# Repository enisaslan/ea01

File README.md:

# ea01
Plant Irrigation Controller

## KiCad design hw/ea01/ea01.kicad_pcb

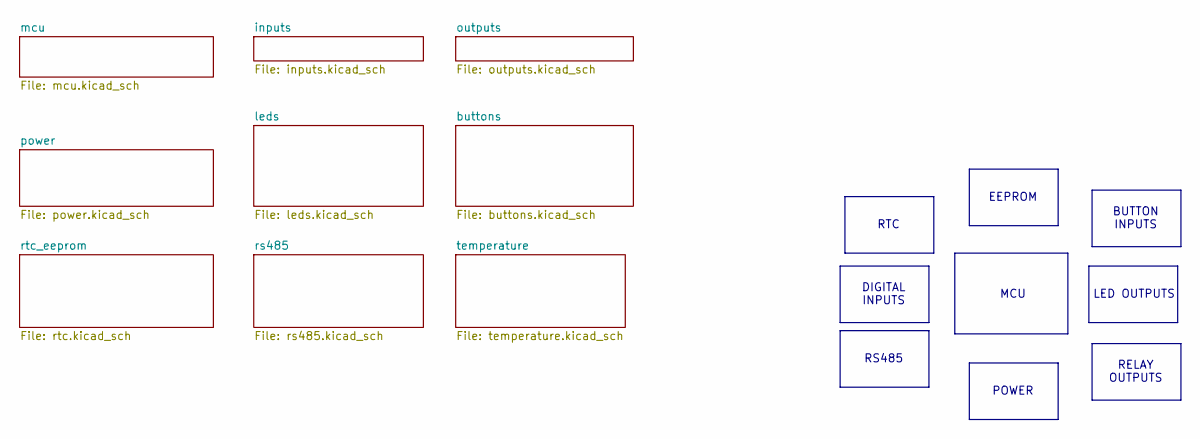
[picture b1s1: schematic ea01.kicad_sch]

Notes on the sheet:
DIGITAL INPUTS
EEPROM
LED OUTPUTS
MCU
RS485
RTC
BUTTON INPUTS
POWER
RELAY OUTPUTS

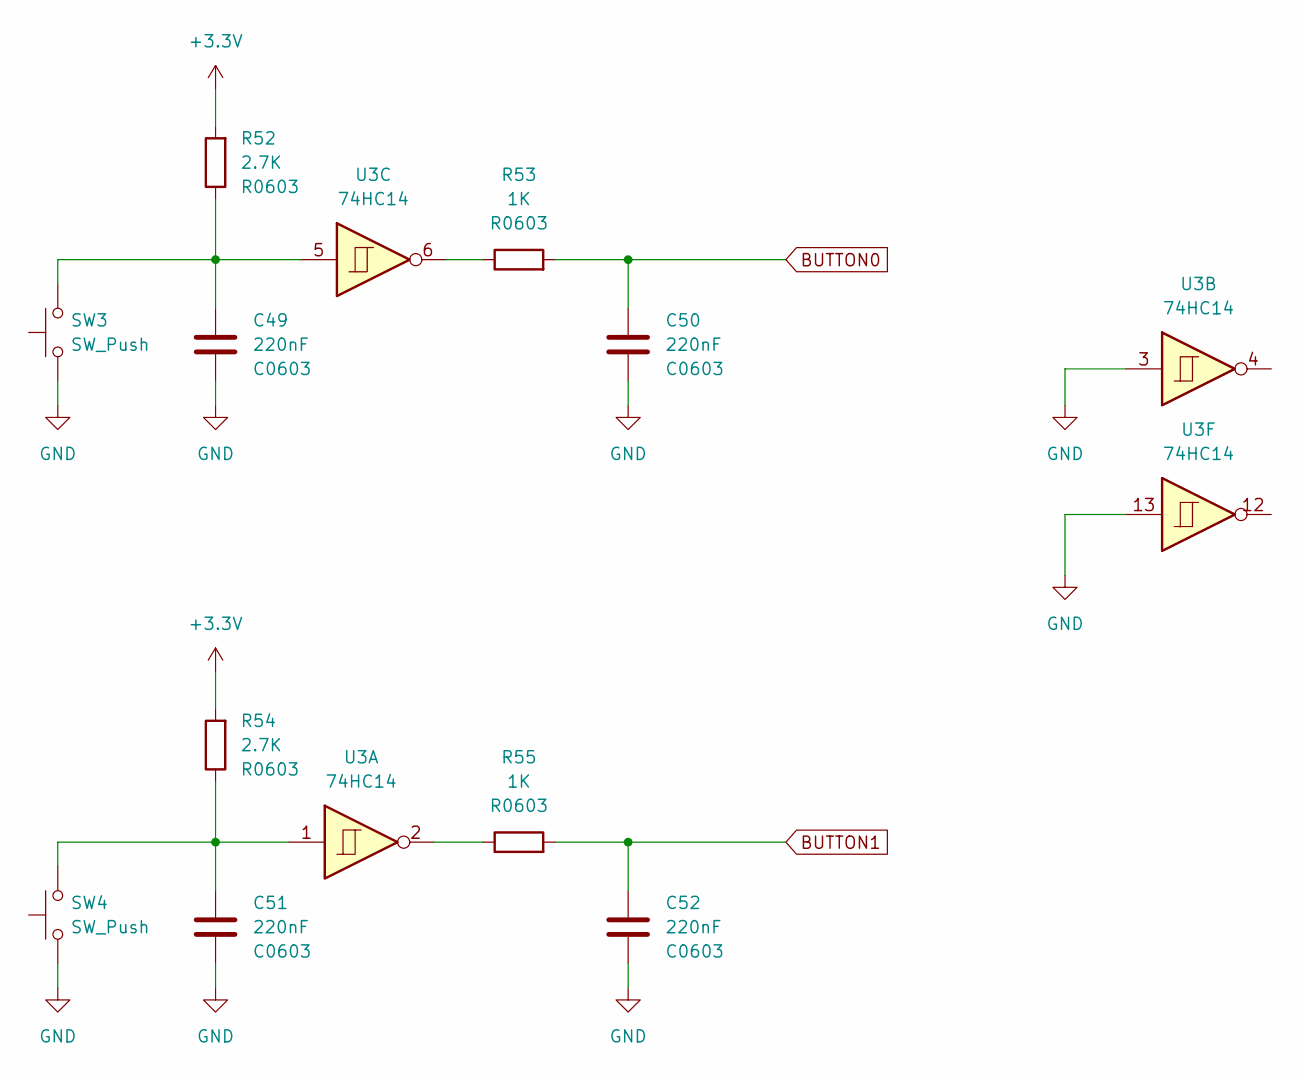
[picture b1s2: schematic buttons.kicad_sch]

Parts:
C49, C50, C51, C52: 220nF; C_0603_1608Metric
R52, R54: 2.7K; R_0603_1608Metric
R53, R55: 1K; R_0603_1608Metric
SW3, SW4: SW_Push; SW_PUSH_6mm_H5mm
U3: 74HC14; SOIC-14_3.9x8.7mm_P1.27mm

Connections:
+3.3V: R52.2, R54.2; also elsewhere on the board
BUTTON0: C50.1, R53.2; also elsewhere on the board
BUTTON1: C52.1, R55.2; also elsewhere on the board
GND: C49.2, C50.2, C51.2, C52.2, SW3.1, SW4.1, U3.3, U3.13; also elsewhere on the board
unnamed: C49.1, R52.1, SW3.2, U3.5
unnamed: C51.1, R54.1, SW4.2, U3.1
unnamed: R53.1, U3.6
unnamed: R55.1, U3.2

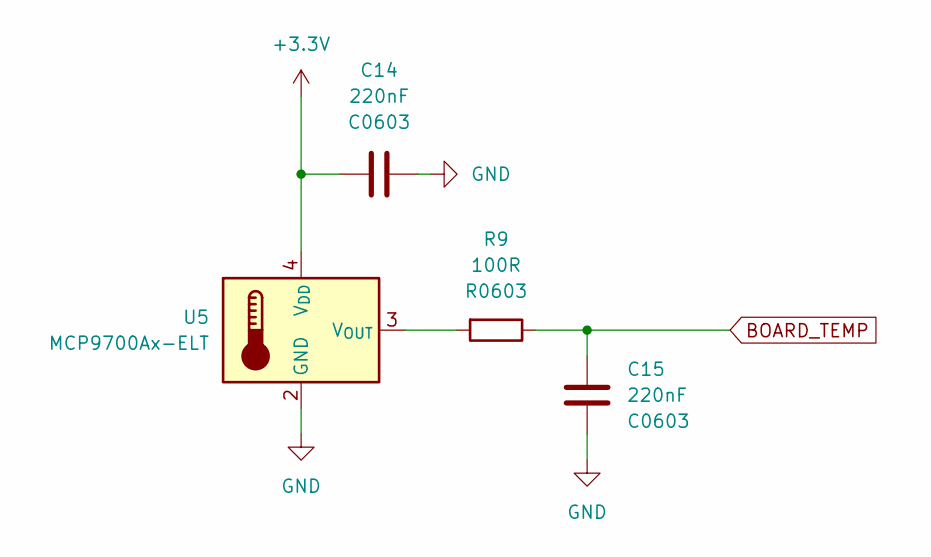
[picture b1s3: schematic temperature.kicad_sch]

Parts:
C14, C15: 220nF; C_0603_1608Metric
R9: 100R; R_0603_1608Metric
U5: MCP9700Ax-ELT; SOT-353_SC-70-5

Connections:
+3.3V: C14.1, U5.4 (V_{DD}); also elsewhere on the board
BOARD_TEMP: C15.1, R9.1; also elsewhere on the board
GND: C14.2, C15.2, U5.2 (GND); also elsewhere on the board
unnamed: R9.2, U5.3 (V_{OUT})

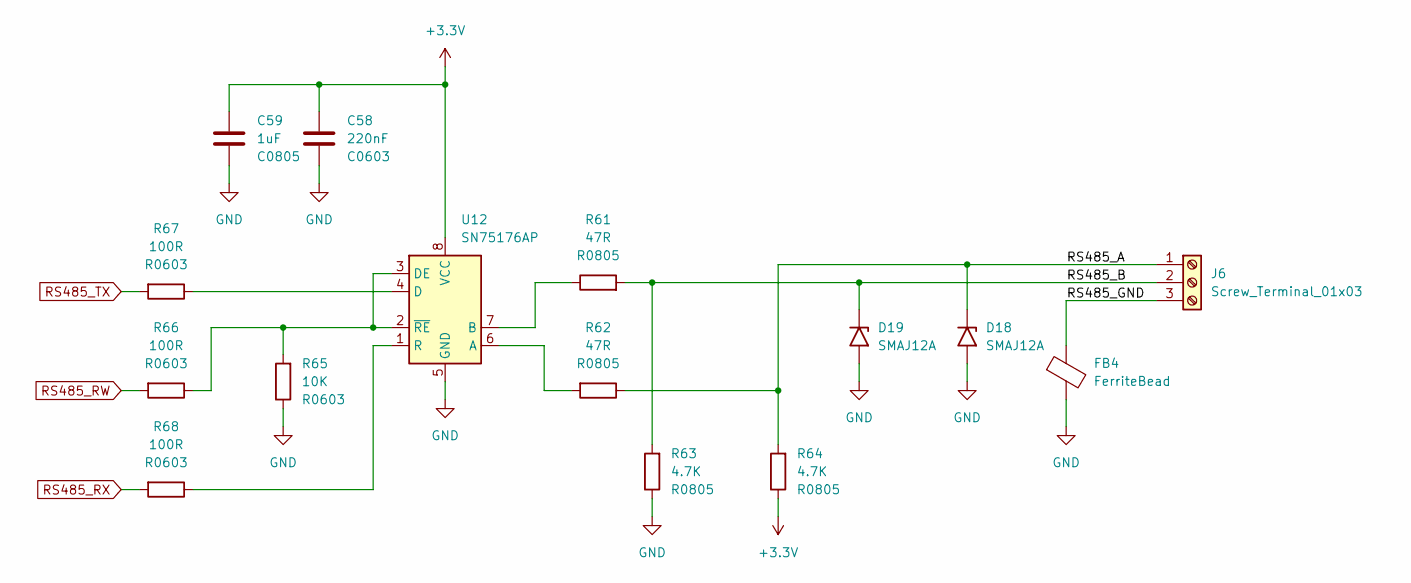
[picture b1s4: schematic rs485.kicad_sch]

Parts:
C58: 220nF; C_0603_1608Metric
C59: 1uF; C_0805_2012Metric
D18, D19: SMAJ12A; D_SMA
FB4: FerriteBead; R_0805_2012Metric
J6: Screw_Terminal_01x03; TerminalBlock_bornier-3_P5.08mm
R61, R62: 47R; R_0805_2012Metric
R63, R64: 4.7K; R_0805_2012Metric
R65: 10K; R_0603_1608Metric
R66, R67, R68: 100R; R_0603_1608Metric
U12: SN75176AP; DIP-8_W7.62mm

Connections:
+3.3V: C58.1, C59.1, R64.1, U12.8 (VCC); also elsewhere on the board
/rs485/RS485_A: D18.1 (A1), J6.1, R62.1, R64.2
/rs485/RS485_B: D19.1 (A1), J6.2, R61.2, R63.2
/rs485/RS485_GND: FB4.1, J6.3
GND: C58.2, C59.2, D18.2 (A2), D19.2 (A2), FB4.2, R63.1, R65.1, U12.5 (GND); also elsewhere on the board
unnamed: R62.2, U12.6 (A)
unnamed: R61.1, U12.7 (B)
unnamed: R67.1, U12.4 (D)
unnamed: R65.2, R66.1, U12.2 (~RE), U12.3 (DE)
unnamed: R68.1, U12.1 (R)
RS485_RW: R66.2; also elsewhere on the board
RS485_RX: R68.2; also elsewhere on the board
RS485_TX: R67.2; also elsewhere on the board

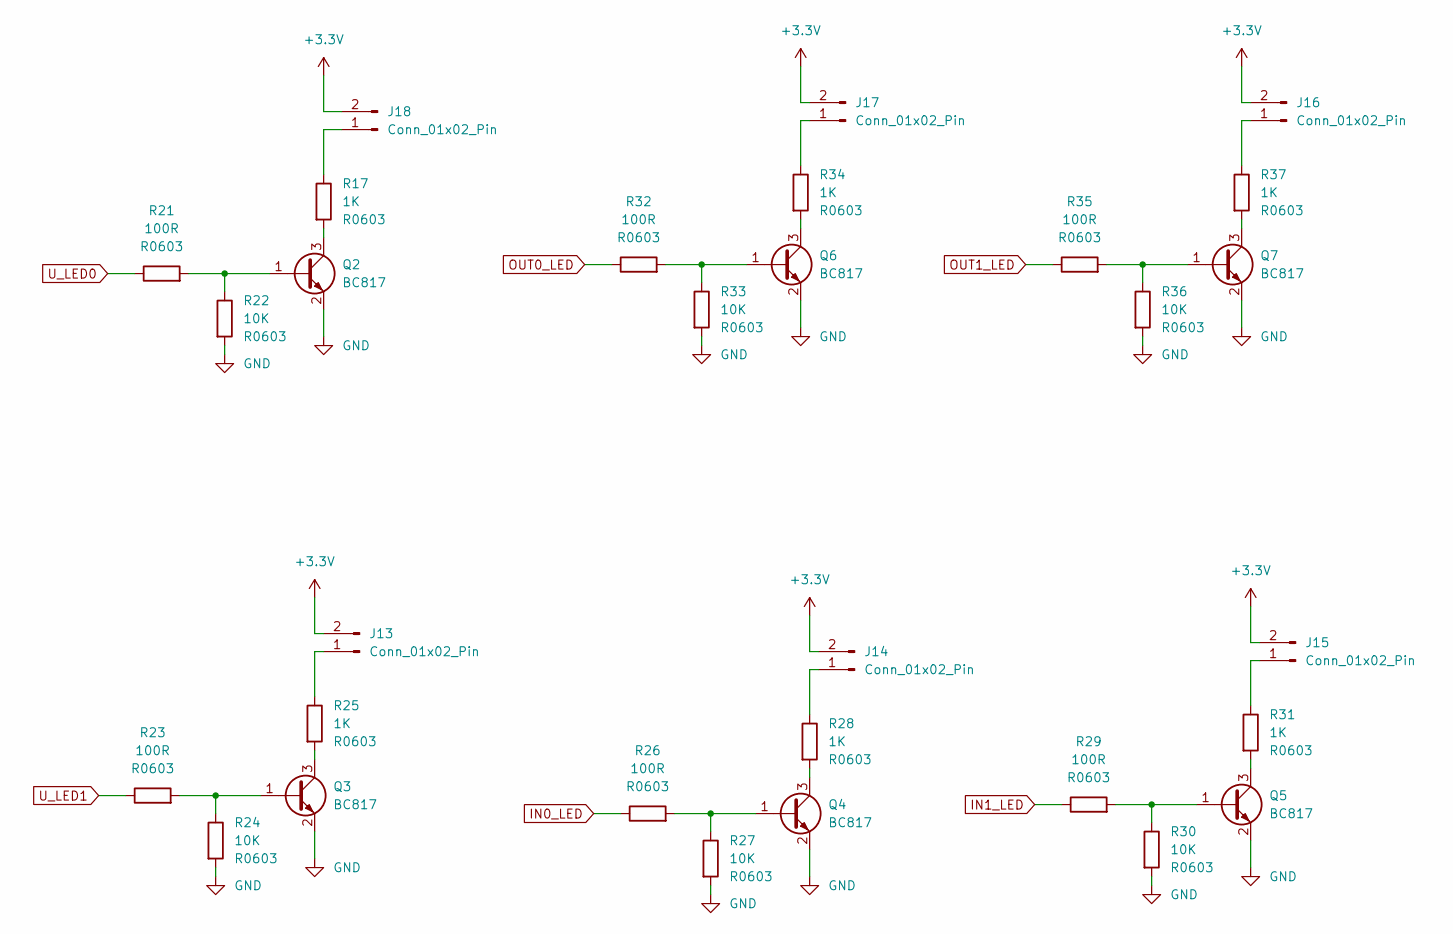
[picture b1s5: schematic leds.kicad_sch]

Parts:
J13, J14, J15, J16, J17, J18: Conn_01x02_Pin; PinHeader_1x02_P1.27mm_Vertical
Q2, Q3, Q4, Q5, Q6, Q7: BC817; SOT-23
R17, R25, R28, R31, R34, R37: 1K; R_0603_1608Metric
R21, R23, R26, R29, R32, R35: 100R; R_0603_1608Metric
R22, R24, R27, R30, R33, R36: 10K; R_0603_1608Metric

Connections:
+3.3V: J13.2, J14.2, J15.2, J16.2, J17.2, J18.2; also elsewhere on the board
GND: Q2.2 (E), Q3.2 (E), Q4.2 (E), Q5.2 (E), Q6.2 (E), Q7.2 (E), R22.2, R24.2, R27.2, R30.2, R33.2, R36.2; also elsewhere on the board
IN0_LED: R26.1; also elsewhere on the board
IN1_LED: R29.1; also elsewhere on the board
unnamed: J13.1, R25.1
unnamed: J14.1, R28.1
unnamed: J15.1, R31.1
unnamed: J16.1, R37.1
unnamed: J17.1, R34.1
unnamed: J18.1, R17.1
unnamed: Q2.1 (B), R21.2, R22.1
unnamed: Q2.3 (C), R17.2
unnamed: Q3.1 (B), R23.2, R24.1
unnamed: Q3.3 (C), R25.2
unnamed: Q4.1 (B), R26.2, R27.1
unnamed: Q4.3 (C), R28.2
unnamed: Q5.1 (B), R29.2, R30.1
unnamed: Q5.3 (C), R31.2
unnamed: Q6.1 (B), R32.2, R33.1
unnamed: Q6.3 (C), R34.2
unnamed: Q7.1 (B), R35.2, R36.1
unnamed: Q7.3 (C), R37.2
OUT0_LED: R32.1; also elsewhere on the board
OUT1_LED: R35.1; also elsewhere on the board
U_LED0: R21.1; also elsewhere on the board
U_LED1: R23.1; also elsewhere on the board

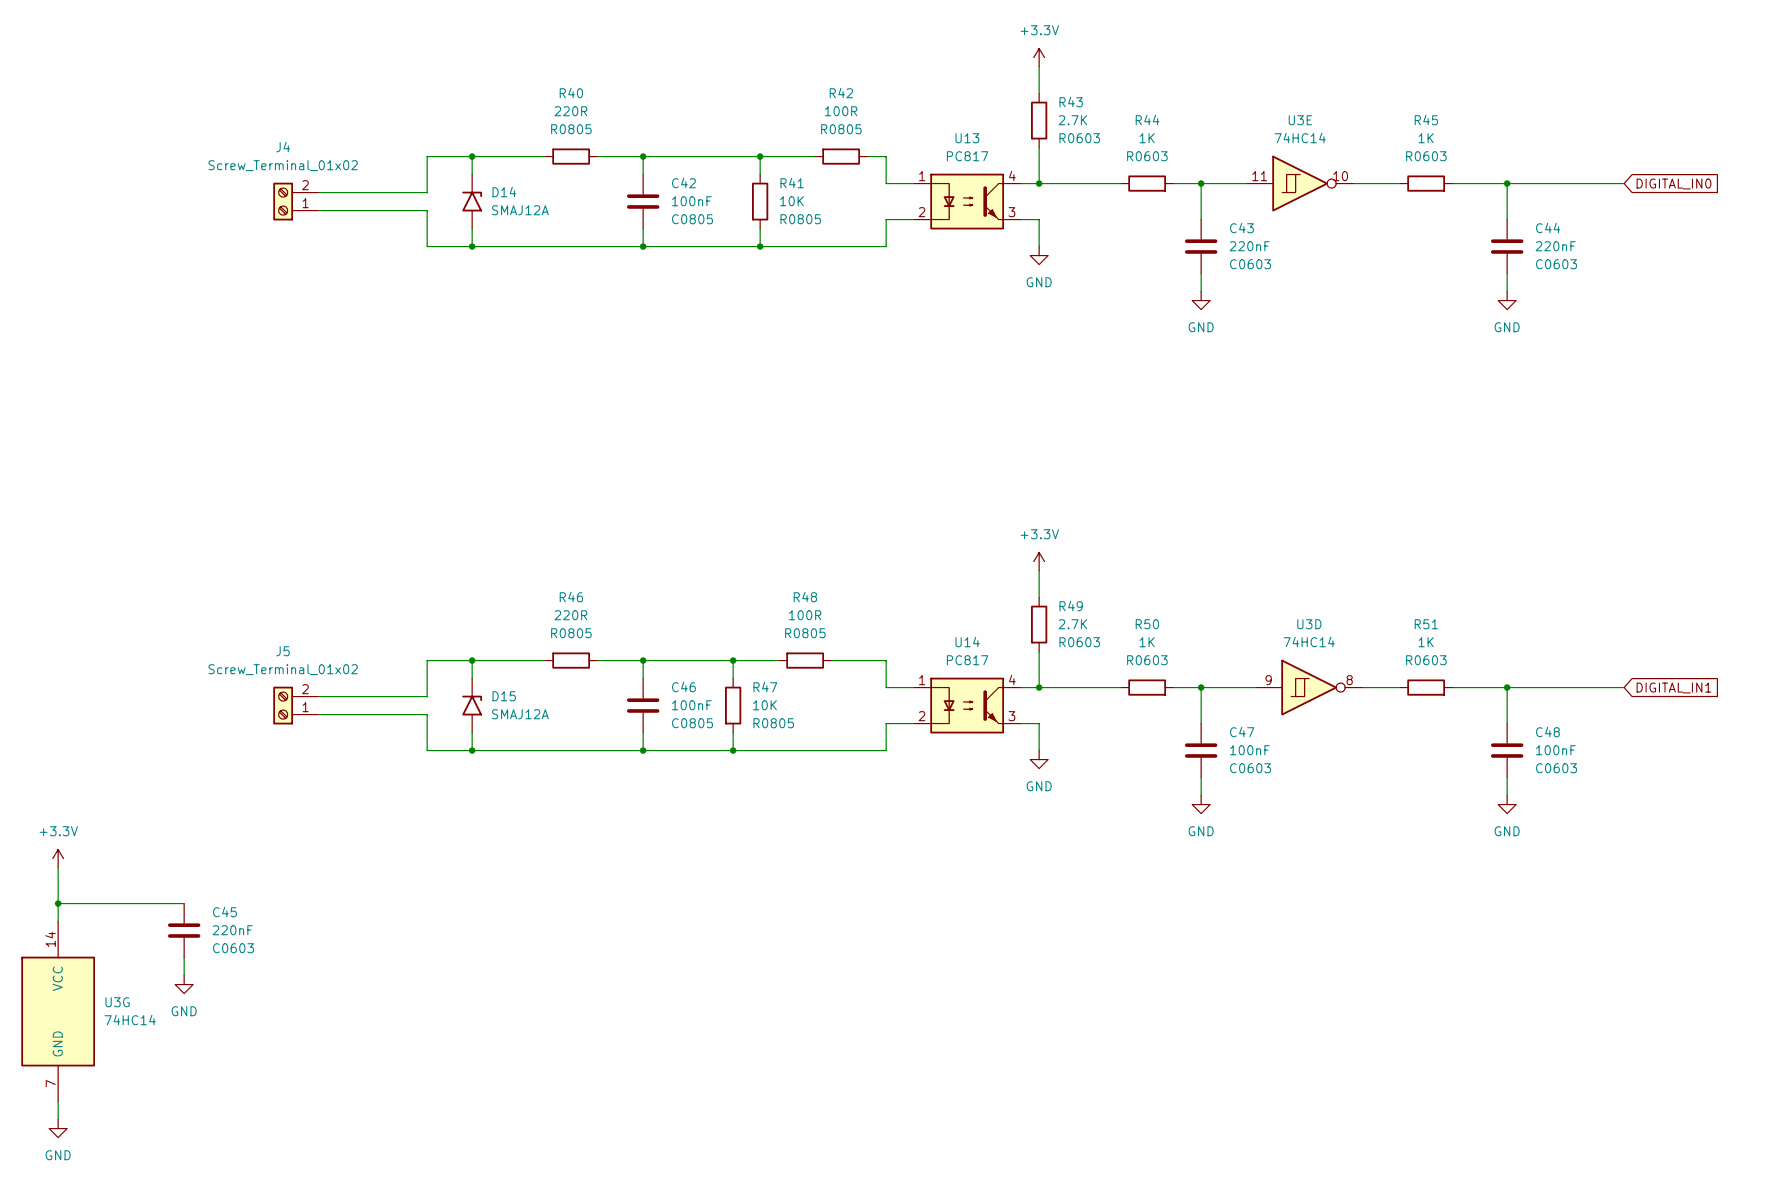
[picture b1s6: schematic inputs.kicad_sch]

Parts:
C42, C46: 100nF; C_0805_2012Metric
C43, C44, C45: 220nF; C_0603_1608Metric
C47, C48: 100nF; C_0603_1608Metric
D14, D15: SMAJ12A; D_SMA
J4, J5: Screw_Terminal_01x02; TerminalBlock_bornier-2_P5.08mm
R40, R46: 220R; R_0805_2012Metric
R41, R47: 10K; R_0805_2012Metric
R42, R48: 100R; R_0805_2012Metric
R43, R49: 2.7K; R_0603_1608Metric
R44, R45, R50, R51: 1K; R_0603_1608Metric
U3: 74HC14; SOIC-14_3.9x8.7mm_P1.27mm
U13, U14: PC817; DIP-4_W7.62mm

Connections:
+3.3V: C45.1, R43.1, R49.1, U3.14 (VCC); also elsewhere on the board
DIGITAL_IN0: C44.1, R45.2; also elsewhere on the board
DIGITAL_IN1: C48.1, R51.2; also elsewhere on the board
GND: C43.2, C44.2, C45.2, C47.2, C48.2, U3.7 (GND), U13.3, U14.3; also elsewhere on the board
unnamed: C42.1, R40.1, R41.1, R42.2
unnamed: C43.1, R44.2, U3.11
unnamed: C46.1, R46.1, R47.1, R48.2
unnamed: C47.1, R50.2, U3.9
unnamed: D14.1 (A1), J4.2, R40.2
unnamed: C42.2, D14.2 (A2), J4.1, R41.2, U13.2
unnamed: D15.1 (A1), J5.2, R46.2
unnamed: C46.2, D15.2 (A2), J5.1, R47.2, U14.2
unnamed: R42.1, U13.1
unnamed: R43.2, R44.1, U13.4
unnamed: R45.1, U3.10
unnamed: R48.1, U14.1
unnamed: R49.2, R50.1, U14.4
unnamed: R51.1, U3.8

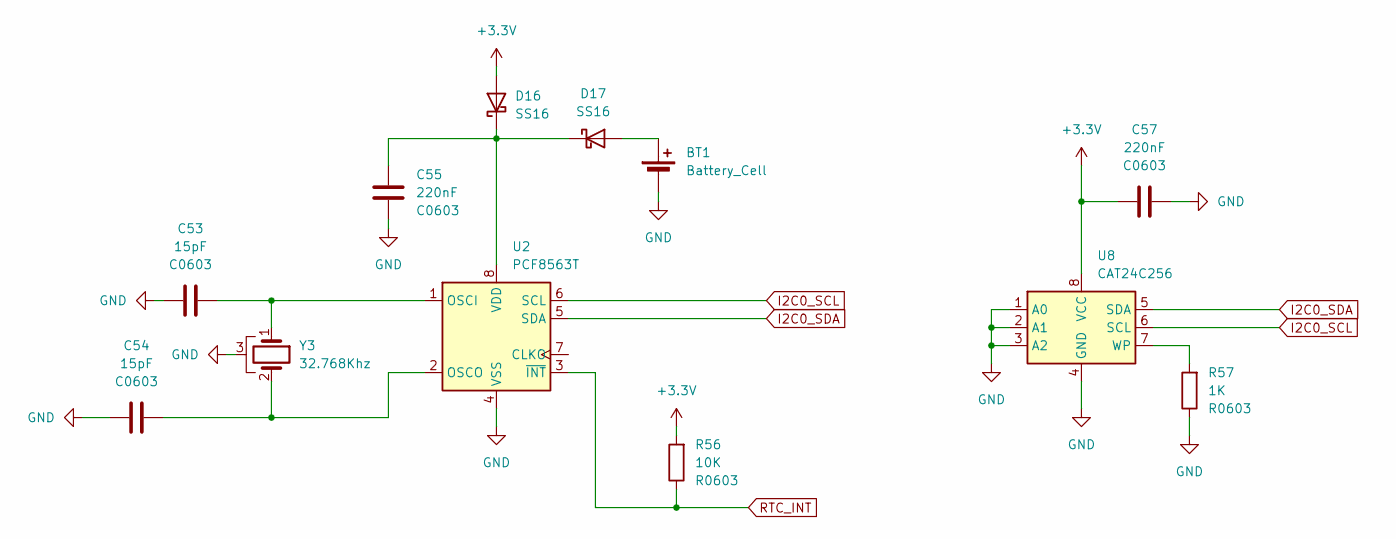
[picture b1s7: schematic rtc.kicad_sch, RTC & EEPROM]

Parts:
BT1: Battery_Cell; PinHeader_1x02_P2.54mm_Vertical
C53, C54: 15pF; C_0603_1608Metric
C55, C57: 220nF; C_0603_1608Metric
D16, D17: SS16; D_MiniMELF
R56: 10K; R_0603_1608Metric
R57: 1K; R_0603_1608Metric
U2: PCF8563T; SOIC-8_3.9x4.9mm_P1.27mm
U8: CAT24C256; SOIC-8_3.9x4.9mm_P1.27mm
Y3: 32.768Khz; Crystal_C38-LF_D3.0mm_L8.0mm_Horizontal_1EP_style1

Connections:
+3.3V: C57.1, D16.2 (A), R56.2, U8.8 (VCC); also elsewhere on the board
GND: BT1.2 (-), C53.1, C54.1, C55.2, C57.2, R57.1, U2.4 (VSS), U8.1 (A0), U8.2 (A1), U8.3 (A2), U8.4 (GND), Y3.3; also elsewhere on the board
I2C0_SCL: U2.6 (SCL), U8.6 (SCL); also elsewhere on the board
I2C0_SDA: U2.5 (SDA), U8.5 (SDA); also elsewhere on the board
unnamed: BT1.1 (+), D17.2 (A)
unnamed: C55.1, D16.1 (K), D17.1 (K), U2.8 (VDD)
unnamed: C53.2, U2.1 (OSCI), Y3.1
unnamed: C54.2, U2.2 (OSCO), Y3.2
unnamed: R57.2, U8.7 (WP)
RTC_INT: R56.1, U2.3 (~INT); also elsewhere on the board

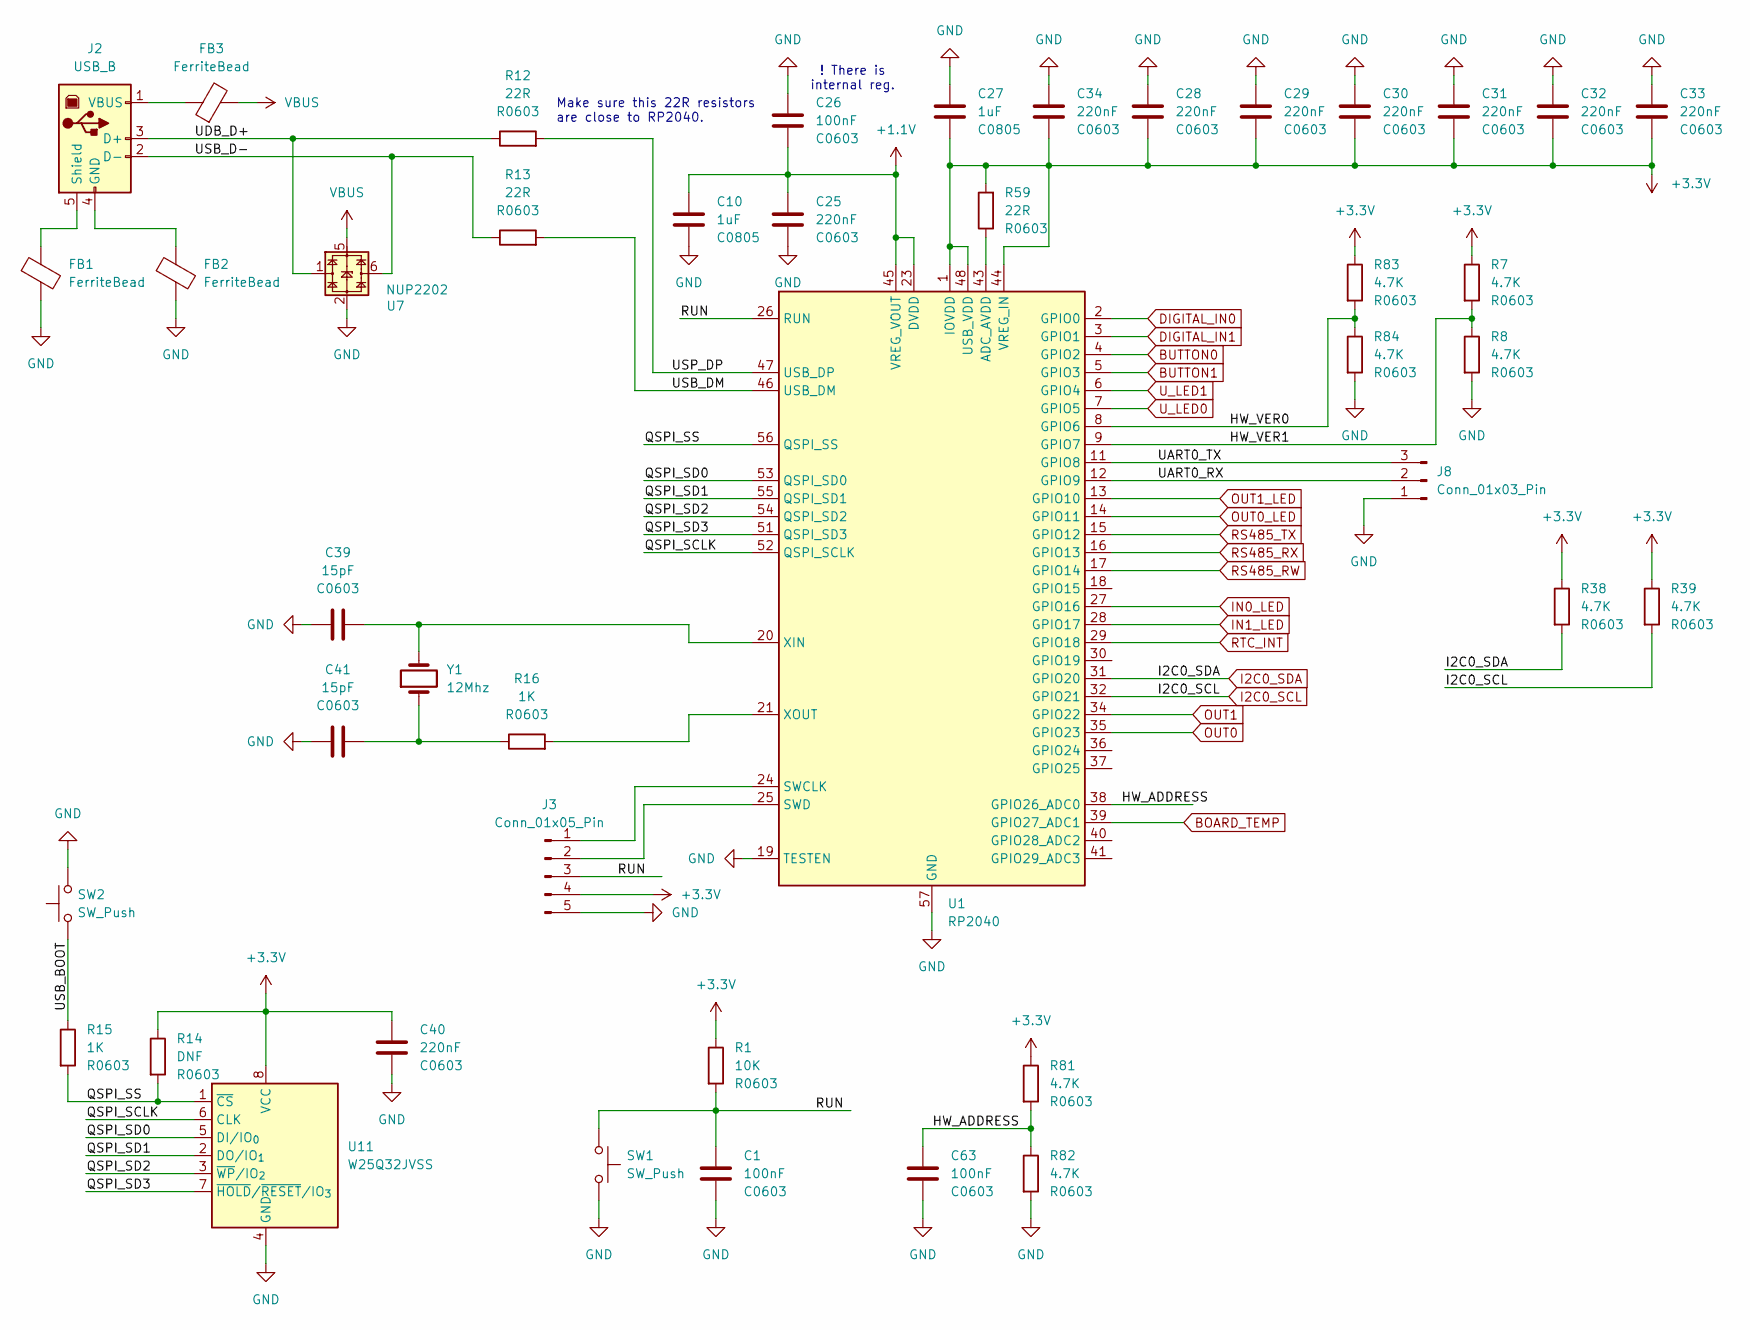
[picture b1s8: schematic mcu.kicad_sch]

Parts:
C1, C26, C63: 100nF; C_0603_1608Metric
C10, C27: 1uF; C_0805_2012Metric
C25, C28, C29, C30, C31, C32, C33, C34, C40: 220nF; C_0603_1608Metric
C39, C41: 15pF; C_0603_1608Metric
FB1, FB2, FB3: FerriteBead; R_0805_2012Metric
J2: USB_B; USB_B_OST_USB-B1HSxx_Horizontal
J3: Conn_01x05_Pin; PinHeader_1x05_P2.54mm_Vertical
J8: Conn_01x03_Pin; PinHeader_1x03_P2.54mm_Vertical
R1: 10K; R_0603_1608Metric
R7, R8, R38, R39, R81, R82, R83, R84: 4.7K; R_0603_1608Metric
R12, R13, R59: 22R; R_0603_1608Metric
R14: DNF; R_0603_1608Metric
R15, R16: 1K; R_0603_1608Metric
SW1, SW2: SW_Push; SW_Tactile_SPST_Angled_PTS645Vx83-2LFS
U1: RP2040; QFN-56-1EP_7x7mm_P0.4mm_EP3.2x3.2mm
U7: NUP2202; SOT-363_SC-70-6
U11: W25Q32JVSS; SOIC-8_5.3x5.3mm_P1.27mm
Y1: 12Mhz; Crystal_SMD_Abracon_ABM3-2Pin_5.0x3.2mm

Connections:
+1.1V: C10.1, C25.1, C26.2, U1.23 (DVDD), U1.45 (VREG_VOUT), U1.50 (DVDD)
+3.3V: C27.2, C28.2, C29.2, C30.2, C31.2, C32.2, C33.2, C34.2, C40.1, J3.4, R1.1, R7.1, R14.1, R38.1, R39.1, R59.2, R81.1, R83.1, U1.1 (IOVDD), U1.10 (IOVDD), U1.22 (IOVDD), U1.33 (IOVDD), U1.42 (IOVDD), U1.44 (VREG_IN), U1.48 (USB_VDD), U1.49 (IOVDD), U11.8 (VCC); also elsewhere on the board
/mcu/HW_ADDRESS: C63.1, R81.2, R82.1, U1.38 (GPIO26_ADC0)
/mcu/HW_VER0: R83.2, R84.1, U1.8 (GPIO6)
/mcu/HW_VER1: R7.2, R8.1, U1.9 (GPIO7)
/mcu/QSPI_SCLK: U1.52 (QSPI_SCLK), U11.6 (CLK)
/mcu/QSPI_SD0: U1.53 (QSPI_SD0), U11.5 (DI/IO_{0})
/mcu/QSPI_SD1: U1.55 (QSPI_SD1), U11.2 (DO/IO_{1})
/mcu/QSPI_SD2: U1.54 (QSPI_SD2), U11.3 (~WP/IO_{2})
/mcu/QSPI_SD3: U1.51 (QSPI_SD3), U11.7 (~HOLD/~RESET/IO_{3})
/mcu/QSPI_SS: R14.2, R15.2, U1.56 (QSPI_SS), U11.1 (~CS)
/mcu/RUN: C1.1, J3.3, R1.2, SW1.1, U1.26 (RUN)
/mcu/UART0_RX: J8.2, U1.12 (GPIO9)
/mcu/UART0_TX: J8.3, U1.11 (GPIO8)
/mcu/UDB_D+: J2.3 (D+), R12.1, U7.1
/mcu/USB_BOOT: R15.1, SW2.1
/mcu/USB_D-: J2.2 (D-), R13.1, U7.6
/mcu/USB_DM: R13.2, U1.46 (USB_DM)
/mcu/USP_DP: R12.2, U1.47 (USB_DP)
BOARD_TEMP: U1.39 (GPIO27_ADC1); also elsewhere on the board
BUTTON0: U1.4 (GPIO2); also elsewhere on the board
BUTTON1: U1.5 (GPIO3); also elsewhere on the board
DIGITAL_IN0: U1.2 (GPIO0); also elsewhere on the board
DIGITAL_IN1: U1.3 (GPIO1); also elsewhere on the board
GND: C1.2, C10.2, C25.2, C26.1, C27.1, C28.1, C29.1, C30.1, C31.1, C32.1, C33.1, C34.1, C39.1, C40.2, C41.1, C63.2, FB1.2, FB2.2, J3.5, J8.1, R8.2, R82.2, R84.2, SW1.2, SW2.2, U1.19 (TESTEN), U1.57 (GND), U7.2, U11.4 (GND); also elsewhere on the board
I2C0_SCL: R39.2, U1.32 (GPIO21); also elsewhere on the board
I2C0_SDA: R38.2, U1.31 (GPIO20); also elsewhere on the board
IN0_LED: U1.27 (GPIO16); also elsewhere on the board
IN1_LED: U1.28 (GPIO17); also elsewhere on the board
unnamed: C41.2, R16.1, Y1.1
unnamed: FB2.1, J2.4 (GND)
unnamed: FB1.1, J2.5 (Shield)
unnamed: FB3.1, J2.1 (VBUS)
unnamed: J3.1, U1.24 (SWCLK)
unnamed: J3.2, U1.25 (SWD)
unnamed: R59.1, U1.43 (ADC_AVDD)
unnamed: C39.2, U1.20 (XIN), Y1.2
unnamed: R16.2, U1.21 (XOUT)
OUT0: U1.35 (GPIO23); also elsewhere on the board
OUT0_LED: U1.14 (GPIO11); also elsewhere on the board
OUT1: U1.34 (GPIO22); also elsewhere on the board
OUT1_LED: U1.13 (GPIO10); also elsewhere on the board
RS485_RW: U1.17 (GPIO14); also elsewhere on the board
RS485_RX: U1.16 (GPIO13); also elsewhere on the board
RS485_TX: U1.15 (GPIO12); also elsewhere on the board
RTC_INT: U1.29 (GPIO18); also elsewhere on the board
U_LED0: U1.7 (GPIO5); also elsewhere on the board
U_LED1: U1.6 (GPIO4); also elsewhere on the board
VBUS: FB3.2, U7.5; also elsewhere on the board

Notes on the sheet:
! There is internal reg.
Make sure this 22R resistors are close to RP2040.

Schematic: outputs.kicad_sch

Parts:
C62: 470uF; CP_Radial_D8.0mm_P3.50mm
D20, D21: SM4007; D_MELF
FB5, FB6: FerriteBead; R_0805_2012Metric
J10, J11: Screw_Terminal_01x02; TerminalBlock_bornier-2_P5.08mm
K1, K2: G5NB; Relay_SPST_Omron_G5NB
Q9, Q11: BC817; SOT-23
R69, R71, R78, R80: 100R; R_0603_1608Metric
R70, R79: 10K; R_0603_1608Metric

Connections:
+12V: FB5.1; also elsewhere on the board
+12V_RELAY: C62.1, D20.1 (K), D21.1 (K), FB5.2, K1.A1, K2.A1
/outputs/R0_A: J10.1, K1.14
/outputs/R0_B: J10.2, K1.13
/outputs/R1_A: J11.1, K2.14
/outputs/R1_B: J11.2, K2.13
GND: FB6.1; also elsewhere on the board
GND_RELAY: C62.2, FB6.2, Q9.2 (E), Q11.2 (E), R70.2, R79.2
unnamed: D20.2 (A), K1.A2, R71.1
unnamed: D21.2 (A), K2.A2, R80.1
unnamed: Q9.1 (B), R69.2, R70.1
unnamed: Q9.3 (C), R71.2
unnamed: Q11.1 (B), R78.2, R79.1
unnamed: Q11.3 (C), R80.2
OUT0: R69.1; also elsewhere on the board
OUT1: R78.1; also elsewhere on the board

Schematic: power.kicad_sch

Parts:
C2, C9: 470uF; CP_Radial_D8.0mm_P3.50mm
C3, C18, C21, C35: 10uF; C_0805_2012Metric
C4, C12, C22, C23, C36: 220nF; C_0603_1608Metric
C5, C13: 100nF; C_0603_1608Metric
C6, C11: 1uF; C_0805_2012Metric
C7: 220nF; C_0805_2012Metric
C8: 390pF; C_0805_2012Metric
D2, D5: SS26; D_SMA
D6: SMAJ24A; D_SMA
J1: Screw_Terminal_01x02; TerminalBlock_bornier-2_P5.08mm
J7: Conn_01x03_Pin; PinHeader_1x03_P2.54mm_Vertical
J19: Conn_01x02_Pin; PinHeader_1x02_P1.27mm_Vertical
L1: 220uH; L_Coilcraft_MSS1210-XXX
R2, R3, R4: 1R; R_1206_3216Metric
R5: 3.3K; R_0805_2012Metric
R6: 10K; R_0805_2012Metric
R11: 2.7K; R_0603_1608Metric
U4: MC34063AD; SOIC-8_3.9x4.9mm_P1.27mm
U6: AMS1117-3.3; SOT-223-3_TabPin2

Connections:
+3.3V: C18.1, C23.1, R11.1, U6.2 (VO); also elsewhere on the board
+5V: C21.1, C22.1, J7.2, U6.3 (VI)
+5V_REG: C9.1, C11.1, C12.1, C13.1, J7.1, L1.2, R6.1
+12V: C2.1, C3.1, C4.1, C5.1, C6.1, C7.1, D5.1 (K), R2.1, R3.1, R4.1, U4.6 (Vin); also elsewhere on the board
GND: C2.2, C3.2, C4.2, C5.2, C6.2, C7.2, C8.2, C9.2, C11.2, C12.2, C13.2, C18.2, C21.2, C22.2, C23.2, C35.2, C36.2, D2.2 (A), D6.2 (A2), J1.2, J19.1, R5.1, U4.4 (GND), U6.1 (GND); also elsewhere on the board
unnamed: D2.1 (K), L1.1, U4.2 (SwE)
unnamed: D5.2 (A), D6.1 (A1), J1.1
unnamed: J19.2, R11.2
unnamed: R2.2, R3.2, R4.2, U4.1 (SwC), U4.7 (Ipk), U4.8 (DC)
unnamed: C8.1, U4.3 (TC)
unnamed: R5.2, R6.2, U4.5 (Vfb)
VBUS: C35.1, C36.1, J7.3; also elsewhere on the board

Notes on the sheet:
------------------------ 100Khz(Max) = 100pF 50Khz = 220pF 30Khz = 330pF 25Khz(Ideal) = 390pF 20Khz = 470pF ------------------------

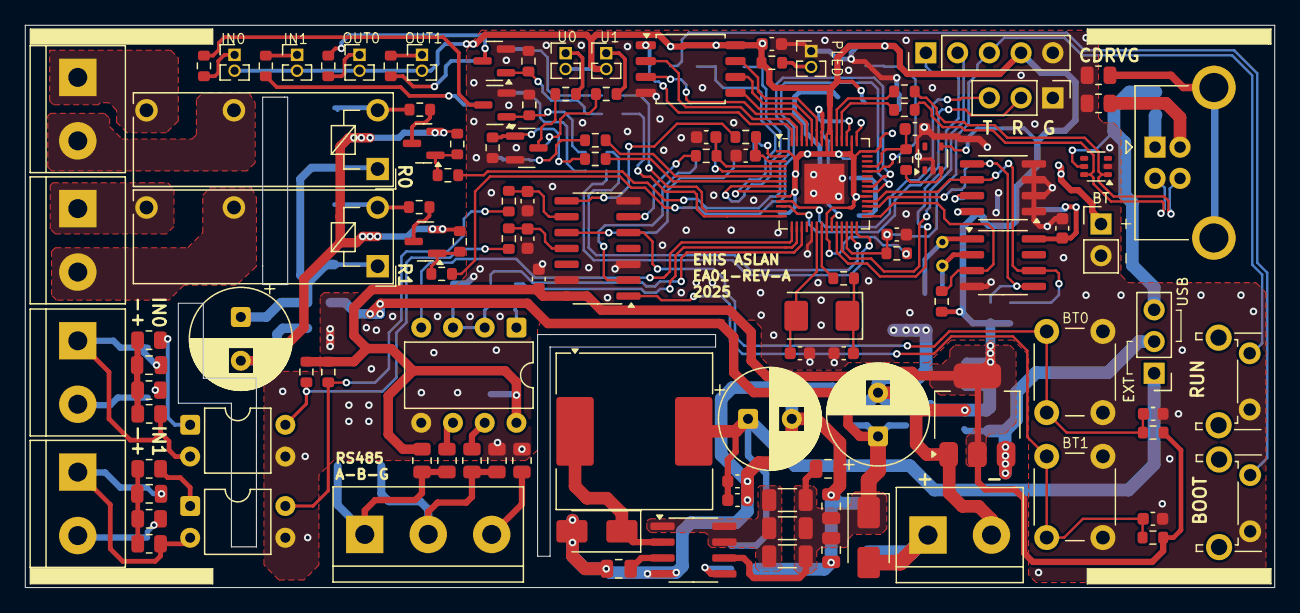
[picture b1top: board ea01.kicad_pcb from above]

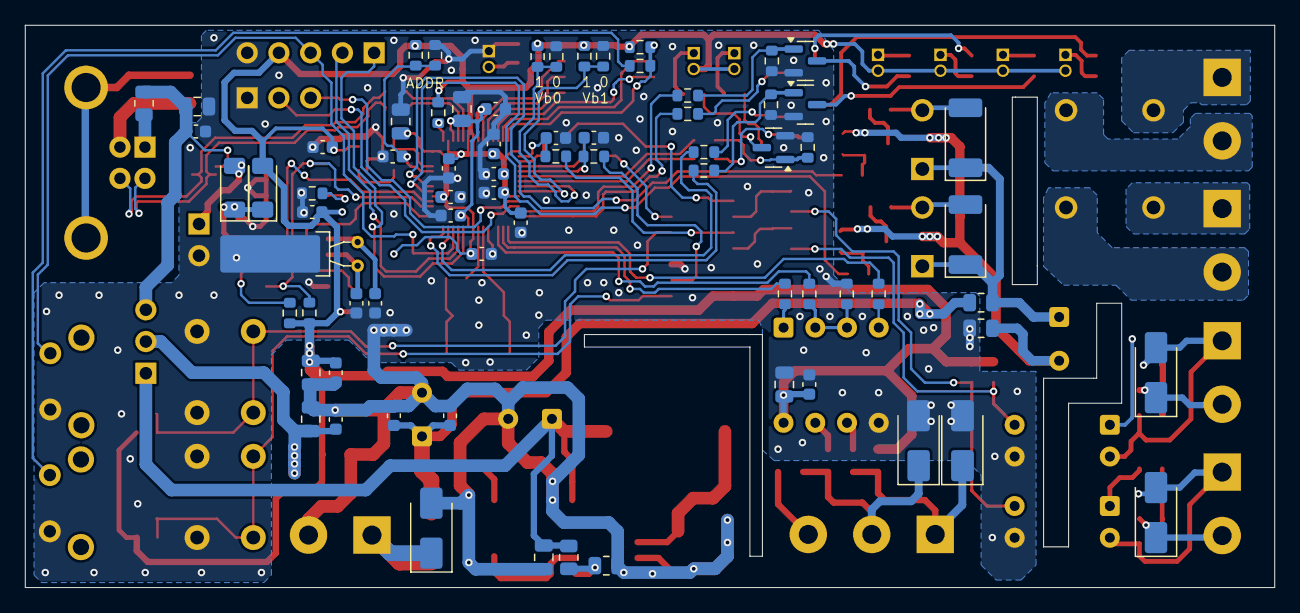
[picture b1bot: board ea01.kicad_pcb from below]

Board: 2 copper layers, 100.0 x 45.0 mm, 189 parts (72 on the bottom side), 120 nets.

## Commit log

2025-07-20 data added.
2025-07-20 first upload.
2025-07-20 gitignore file added
2025-07-20 backup data deleted and ignored for github
2025-07-20 schmatic drawing continue...
2025-07-23 sch refactored
2025-09-02 errors fix for comp fp
2025-09-13 pcb drawing continue..
2025-09-19 component placement continue..
2025-09-19 placement continue...
2025-09-19 placement optimization and review continue
2025-09-21 placement completed.
2025-09-21 update..
2025-09-21 drawing continue...
2025-09-22 Stop tracking hw/ea01/ea01-backups folder
2025-09-26 drawing continue..
2025-09-28 draw contleted. Not checked yet.
2025-09-28 update.
2025-09-28 gerber files generated..
2025-09-29 3d models updated
2025-09-30 Order Data git add .!
2025-11-13 gnd connection update
